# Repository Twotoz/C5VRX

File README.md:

<div align="center">

  <p><strong>ESP32-C5 Analog 5.8 GHz FPV Receiver</strong></p>
  <p>From live 5.8 GHz FPV video to real-time analog CVBS with one Seeed Studio XIAO ESP32-C5 and a passive resistor DAC.</p>

  <p>

  </p>

</div>

---

C5VRX-5 receives analog 5.8 GHz FPV video with the ESP32-C5's own radio and
outputs composite PAL/NTSC through a passive 6-bit resistor DAC: automatic
gain control, a quick baseline boot with manual calibration, an on-screen
menu, and browser-based flashing and controls.

The default demodulator is **U50P64-R1**, the U80P64-R1 formulas with loop
gain 0.50: less picture noise for a VTX of deviation up to about 1.0 at the
cost of detail and colour level. A VTX measured wider falls back to
**U80P64-R1** ([evidence and limits](docs/P64.md)), which has one positive
NTSC check. U50P64-R1 is host-tested only; PAL, weak-signal behaviour and
range still need hardware validation. Board findings, including the retired U85Q/kp/LP models
and the removed sync flywheel, are in [docs/FINDINGS.md](docs/FINDINGS.md).

## Experimental firmware — flight safety warning

> [!WARNING]
> **C5VRX is an experimental FPV receiver. Bugs, signal loss, automatic
> receive-chain changes or incompatibility with your camera/goggles can cause
> sudden loss of video or sync, even after an apparently successful test.
> Loss of FPV video can lead to a crash, property damage or serious injury.**
> Do not rely on C5VRX as your only means of maintaining safe control of an aircraft.

- **Test every firmware, hardware and settings combination on the ground
  first**, propellers removed: startup, calibration, weak signal, recovery
  after video loss, with your own camera and goggles.
- **Keep disruptive actions on the ground.** Calibration, scanning, channel
  changes, the menu, DAC tests and diagnostics can interrupt the picture;
  never flash or run bench tests in flight.
- **Automatic changes are experimental too.** Live filter/profile switching
  (default on; console `A` turns it off, `T` shows the state) and live
  OUTPUT/format changes restart part of the pipeline and may interrupt video.
- **Fly tests in a controlled area** clear of people, traffic and property,
  close by, with a safe way to recover if video disappears, and within local
  rules (visual line of sight, observers).
- **A release, a "Latest" label or green CI is not flight qualification.**
  PR builds are development builds; a test of an earlier build does not
  validate later changes.
- **Report video loss** with the exact firmware version, hardware, settings,
  steps and any logs/DVR footage, and investigate on the ground before flying
  again.

The firmware is provided under [GPL-3.0-only](LICENSE), including its warranty
and liability provisions in sections 15–17, to the extent permitted by
applicable law. This warning does not replace those terms or limit rights
that cannot legally be excluded.

## Video

[C5VRX-5 vs C5VRX-4 flight range test by Louis Hitchcock](https://www.youtube.com/watch?v=Gp3xmLrn_34).

## Hardware

A Seeed Studio XIAO ESP32-C5 and seven resistors; no extra RF parts
([schematic](docs/hardware/c5vrx-dac-schematic.png)). Six resistors, one per
pin, join on one node, the CVBS output; the seventh loads that node to GND.

| XIAO pin | GPIO | DAC bit | Resistor to the output node |
| --- | ---: | --- | ---: |
| D4 | 23 | bit 0 (LSB) | 8.2 kΩ |
| D5 | 24 | bit 1 | 3.9 kΩ |
| D6 | 11 | bit 2 | 2.0 kΩ |
| D7 | 12 | bit 3 | 1.0 kΩ |
| D8 | 8 | bit 4 | 470 Ω |
| D9 | 9 | bit 5 (MSB) | 240 Ω |
| GND | - | load | 200 Ω (output node to GND) |

```
D4 --[8.2k]--+
D5 --[3.9k]--+
D6 --[2.0k]--+
D7 --[1.0k]--+-----------> CVBS out (goggle / monitor AV-in, video)
D8 --[470R]--+     |
D9 --[240R]--+   [200R]   (optional: 470 pF from the node to GND,
                   |        improvement unproven)
GND ---------------+------> GND (goggle / monitor AV-in ground)
```

- **Pin order matters**: 8.2k on D4, 240R on D9. A swapped pair gives a
  scrambled, banded picture.
- Connect the node to the video input (tip) of the goggles, DVR or monitor,
  with a common ground. Standard E24 1 % resistors are fine; keep the wires
  short. Power comes over USB-C or the 5 V pin.
- The video level is **OUTPUT** in the menu (0.5–5.0x, saved; high levels
  can clip). EXPERIMENTAL > AUTO OUTPUT (off by default) lets it follow the
  VTX while OUTPUT is 1.0x; every change it makes is a short (~5 ms) video
  restart.
- **Check the build with the DAC self-test** (`Z` or menu DAC TEST) before
  chasing picture problems: see
  [Building and testing the resistor DAC](docs/hardware/dac-build-and-test.md).

IQ routing is internal (no wiring) and uses GPIO27 (the user LED, which may
glow) and GPIO2. The planned seven/eight-bit DAC expansion is cancelled;
firmware stays six-bit. Leave the carrier's optional R8/R9 unpopulated and
SJ2/SJ3 open.

### Optional external LNA (more range)

C5VRX-5 now supports an external low-noise amplifier in front of the
XIAO. Tested with the **Zeenko ZK06-UM** (10 MHz–6 GHz, SMA;
datasheet at 5.8 GHz: ~22.6 dB gain, ~1.0 dB noise figure), listed under
[Build components](#build-components).

- **Wiring:** antenna → LNA input → LNA output → IPX (U.FL) to SMA pigtail
  → the XIAO's IPX antenna connector (both listed under
  [Build components](#build-components)). Mind the arrow on the LNA: it
  points from the antenna to the receiver. Keep the antenna-to-LNA cable as
  short as possible: every dB lost before the LNA is lost range. Power the
  LNA as its seller specifies.
- **No setting needed.** The firmware measures its own receiver noise and
  follows it: the gain stops where the LNA's noise would fold the 4-bit IQ
  (about G67 with this LNA, G83 without), and the noise reference, signal
  meter, AGC and live DC model adapt by themselves. Fitting or removing the
  LNA needs no calibration. Let the receiver see a few seconds without a
  VTX on its channel after the first boot with a new front end.
- **What it gives:** the receiver's noise figure drops from ~6 dB to ~1 dB.
  In a first indoor walk (a small house, rooms and cupboards) the picture
  held to about **6.5 dB weaker signals** than the bare receiver on the
  previous firmware (50 % picture near −93 dBm at the antenna against
  −86.5 dBm). How much distance that is depends on the surroundings: about
  1.5–1.7× in built-up areas, more in open space; an outdoor A/B is still to
  come.
- **Close in** the LNA's extra gain uses up the lowest gain rows sooner;
  STRONG LANE (EXPERIMENTAL, on by default) takes over when even the lowest
  row folds. EXPERIMENTAL > LEVEL TOP (9 default; 6 / 12 / 16) sets how much
  noise the top gain row may carry.

Details and measurements: [docs/FINDINGS.md](docs/FINDINGS.md), "Received
level at the chip pin" and the external LNA notes.

### Optional digital video capture: Clock Pin D10

In **EXPERIMENTAL**, set **Clock Pin D10** to **ON**, then power off and
move the existing **bit 2 / 2.0 kohm branch from D6/GPIO11 to D3/GPIO7**.
On the next boot, D10/GPIO10 exports the **40 MHz PARLIO TX clock**, and
bit 2 uses D3. OFF is the default and retains the original D4-D9 wiring;
turning it off also needs a reboot and moving the branch back. The menu
shows a reboot warning until the requested setting matches the active one.
The ordinary PR firmware includes this option; no custom build is needed.

For FPGA capture, tap the data pins **before the resistors**, use 3.3 V
inputs and a common ground. With the option active, bit order low to high is
D4, D5, **D3**, D7, D8, D9. D6 is disconnected from TX. Data shifts on
falling clock edges; capture on rising edges and verify timing on your board.
The bus is still six-bit composite video: live samples are identical pairs
`[D,D]` at TX40, **20 MS/s unique codes**. The original colour burst is
preserved; the external device owns sync recovery and colour decoding.
Menu/startup rasters also use this bus. Halted TX/restarts can interrupt the
clock and video; the capture device must reacquire. Console **T** reports
`SAMPLE_CLOCK` with active/requested state, pin, rate and DAC-bit-2 pin.

This extends [LAP87's capture tests](https://github.com/Twotoz/C5VRX/issues/256#issuecomment-6530295384).
The GPIO11 bit-2 rising-edge delay reported there (25 ns) motivates the D3
route; a timing fix on D3 is **not yet verified**. GPIO2 remains IQ-owned.
DAC TEST labels bit 2 as D3 when active; in `tools/dac_check.py`, enter
that branch's measurement using the existing `--d6` argument.
USB DTR/RTS can trigger the ESP32-C5 USB-Serial-JTAG reset/boot behaviour;
there is no deliberate host-DTR gate in the video stream.

### DIY Carrier PCB — REV C: Fat Shark Module + 3.5 mm AV Jack

**[C5VRX_JACK_DIY_V3 / REV C](hardware/C5VRX_JACK_DIY_V3)** is the latest proposed DIY carrier revision for the Seeed Studio XIAO ESP32-C5. It keeps the REV B layout (Fat Shark module-bay outline, 3.5 mm PJ-320D AV jack, reserved seventh/eighth DAC branches) and replaces the SJ1 bay-power solder bridge with a through-hole 1N5819 Schottky diode, so USB and the goggle bay can be connected at the same time.

<div align="center">

</div>

| Feature | REV C details |
| --- | --- |
| **Form factor** | 42.51 × 28.80 mm; XIAO, AV jack and bay header keep their REV A positions |
| **AV output** | VIDEO on Fat Shark J1 pin 6 and PJ-320D tip + ring 1; ground on the jack sleeve |
| **Through-hole DAC** | DIN0207 axial ¼ W resistors; existing six branches and 200 Ω shunt retained |
| **Reserved DAC expansion** | R8: 15 kΩ from D10/GPIO10 via SJ2; R9: 33 kΩ from D3/GPIO7 via SJ3 |
| **Bay power** | D1: 1N5819 Schottky (DO-41, through-hole) from bay 5 V to XIAO 5 V; no jumper to open before USB programming |
| **Rear solder jumpers** | SJ2 / BIT 7 and SJ3 / BIT 8: extra DAC branches |
| **Artwork** | C5VRX logos on both sides; REV C and 6–8 BIT DAC markings on the back |

**Current firmware remains six-bit:** leave R8/R9 unpopulated and SJ2/SJ3 open. The old expansion footprints are retained in the PCB artwork only; seven/eight-bit firmware support is cancelled. Use the rewiring above for Clock Pin D10. [Assembly and jumper settings](hardware/C5VRX_JACK_DIY_V3#dac-branches-and-rear-jumpers).

**Downloads:** [Gerbers + drills](hardware/C5VRX_JACK_DIY_V3/exports/C5VRX_JACK_DIY_V3-gerbers.zip) · [KiCad project](hardware/C5VRX_JACK_DIY_V3) · [BOM](hardware/C5VRX_JACK_DIY_V3/BOM.csv) · [Schematic PDF](hardware/C5VRX_JACK_DIY_V3/exports/C5VRX_JACK_DIY_V3-schematic.pdf) · [STEP](hardware/C5VRX_JACK_DIY_V3/exports/C5VRX_JACK_DIY_V3.step) · [Renders](hardware/C5VRX_JACK_DIY_V3/exports/renders/).

KiCad ERC/DRC and schematic/PCB parity checks are clean; REV C has not been built or measured. [REV B](hardware/C5VRX_JACK_DIY_V2) and the original [REV A carrier](hardware/C5VRX_JACK_DIY) remain available with their fabrication files.

## Flashing

- **Browser:** open the [web flasher](https://twotoz.github.io/C5VRX/) in
  desktop Chrome or Edge, choose **C5VRX-5** and a build, and flash. Use
  **Full firmware** when coming from another generation. **Local File**
  flashes your own `.bin`; **Legacy builds** holds archived C5VRX-3 firmware.
- **From source:** ESP-IDF **6.0.2** (filter and DC correction need its exact
  libphy; other versions build with them disabled and a warning):

  ```sh
  idf.py build
  python tools/flash.py PORT          # e.g. COM6 or /dev/ttyACM0
  ```

  Do not use `idf.py flash` on a running receiver: its USB line reset hangs
  the board until USB and battery are removed. `tools/flash.py` enters
  download mode through the firmware instead. Useful options: `--app-only`,
  `--monitor` / `--monitor-only`, `--log FILE`, `--iq DIR` (IQ snapshots),
  `--check` (boot, `T` and `D`; fails on a crash, wrong image or chain
  fault), `--no-key` (board already in the ROM loader). After
  `sdkconfig.defaults` changes, delete `sdkconfig` and rebuild.
- **XIAO ESP32-C5HR8 with 8 MB PSRAM** (optional; the standard image also
  runs without PSRAM, this one panics without it):

  ```sh
  idf.py -B build-psram -DSDKCONFIG=sdkconfig.psram "-DSDKCONFIG_DEFAULTS=sdkconfig.defaults;sdkconfig.psram.defaults" build
  python tools/flash.py PORT --build build-psram --check
  ```

  Flash the full image when switching. Boot `heap_min` rose from ~2.1 KB to
  ~21.9 KB; PAL and long runs are pending
  ([measurements](docs/FINDINGS.md#psram-8-mb-on-the-xiao-now-mapped-board-2026-10-26)).

## First boot

1. The receiver loads saved settings or a fixed baseline; a short
   sampling-phase check runs under the boot logo. There is no automatic
   RF/DC sweep.
2. If repeated measurements show a poor baseline, the menu recommends
   **CALIBRATE**: run it on the ground, preferably with the VTX off. Full RF
   optimization (`B` / web controls) is a separate, longer bench operation.
3. Select the VTX channel or use SCAN (A1 without a saved channel).
4. **CALIBRATE → Download calibration report** in the web controls exports
   read-only board data ([protocol](docs/FASTER_CALIBRATION.md)).

## Controls

**BOOT button:** short press = next channel (menu: next item); hold 0.6 s =
open the menu (menu: select).

**Menu**, one list with every value in view: BAND, CHANNEL, SCAN, VIDEO
(AUTO/NTSC/PAL), FILTER (AUTO/XNARROW/NARROW/NORMAL/WIDE), PHY FILT
(digital filter mode), AFC (ON/OFF), CALIBRATE, OUTPUT (0.5–5.0x), GAIN
(LEVEL/KEEL/RSSI/MAX/fixed), DEMOD (P64/U85Q/U50), DAC TEST, EXIT. It closes after 30 s of
inactivity (5 min in DAC TEST); entering and leaving can interrupt video.
GAIN defaults to **LEVEL**; KEEL and RSSI are kept for comparison
([AGC research](docs/FINDINGS.md)). The automatic models are remembered
across reboots; MAX and fixed gains never are.

**Serial console** (web flasher **Terminal** tab, or 115200 baud): keys are
case-sensitive, without Enter; `h` lists what your firmware supports.

| Key | Action |
| --- | --- |
| `T` / `h` | Status / help |
| `b` / `c` / `s` | Next band / next channel / scan |
| `o` / `n` / `x` / `e` | Open menu / next item / select / exit |
| `v` / `g` / `G` | Video standard / output level / gain |
| `F` / `B` / `C` | Calibrate current filter / full RF optimization / read-only calibration report |
| `Z` | DAC self-test (ground only) |
| `D` / `R` | Health report / per-second field diagnostics |
| `I` / `M` / `L` | IQ snapshot / gain map / bench IQ lane test |
| `A` | Live filter/profile switching on/off (saved) |
| `S` + suite | Bench PHY sensitivity lab, VTX on ([docs](docs/PHY_SENSITIVITY_LAB.md); ground only) |
| `` ` `` | USB download mode |

Live OUTPUT and profile changes share a five-second cooldown and a verified
restart with rollback. The browser terminal and the flasher use the port one
at a time; **Download log** saves the last 120,000 characters.

## Documentation and development

- [DAC build and self-test](docs/hardware/dac-build-and-test.md) ·
  carriers [REV C](hardware/C5VRX_JACK_DIY_V3), [REV B](hardware/C5VRX_JACK_DIY_V2), [REV A](hardware/C5VRX_JACK_DIY)
- [Receiver findings and hardware evidence](docs/FINDINGS.md) ·
  [field-test protocol](docs/FIELD_TEST.md) ·
  [current receiver behaviour](docs/PR212.md)
- [Research ledger](docs/RESEARCH_LEDGER.md) · [research index](research/README.md) ·
  [U85Q research](docs/pr190-key-findings.md) · [contributing](CONTRIBUTING.md)

`main/` is the C5VRX-5 firmware, `web/` the flasher, `test/` host tests,
`docs/` guides and findings, `research/` experiments, `tools/` console and CI
helpers; `legacy/` keeps C5VRX-1 to C5VRX-4 for reference (not built).

CI runs the host and research checks, builds with ESP-IDF 6.0.2 and publishes
`c5vrx5-v5.0.N` releases from `main` and `c5vrx5-pr-N` builds for PRs;
website-only changes create no firmware. Firmware PRs need board tests on the
matching build: host tests do not establish picture compatibility or range.

## Community

Share build photos, questions and feedback on the
[C5VRX Discord](https://discord.gg/3YNgJRHmzD).

## Credits and license

C5VRX-5 is part of [C5VRX](https://github.com/Twotoz/C5VRX) by Twotoz and
the C5VRX contributors; the official website
([twotoz.github.io/C5VRX](https://twotoz.github.io/C5VRX/)) has the project
and its Discord invite. It builds on C5VRX-2..4 (the continuous MODEM_DIAG
to BitScrambler video path, Direct Gain V3-V5, the PAIR schedule and the
U85Q study of PR #190), on zerowidth/C5VRX PR #3 (interference-burst gate,
sampling-phase probe, off-grid channel tuning), on Louis Hitchcock's staged
overload recovery (C5VRX #182/#184), and on ESPARGOS esp-sdr (GPL-3.0) for
the C5 RX filter control. Espressif supplied the GDMA EOF fix
(espressif/esp-idf#19091).

Like the rest of this repository, C5VRX-5 is licensed under
**GPL-3.0-only** (see [LICENSE](LICENSE)). The GPL allows
commercial use, including selling receivers with this firmware, provided
the source (with your changes) is passed on under the same license.

The C5VRX name and logos have separate terms; see [assets/BRANDING.md](assets/BRANDING.md).

## Build components

| Product | Photo | Link / Source |
| --- | --- | --- |
| Seeed Studio XIAO ESP32-C5 |  | [View on Amazon](https://link.amazon/B0gopCVDt) |
| C5VRX_JACK_DIY_V3 / REV C carrier |  | [Gerbers & KiCad files](hardware/C5VRX_JACK_DIY_V3) · [REV B](hardware/C5VRX_JACK_DIY_V2) · [REV A](hardware/C5VRX_JACK_DIY) |
| Perfboard (alternative) |  | [View on Amazon](https://link.amazon/B0i2qqMeq) |
| Resistor kit |  | [View on Amazon](https://link.amazon/B06XSBkln) |
| Zeenko ZK06-UM LNA (optional, [more range](#optional-external-lna-more-range)) |  | [View on Amazon](https://link.amazon/B0iY2ccnV) |
| IPX (U.FL) to SMA pigtail (XIAO to the LNA) |  | [View on Amazon](https://link.amazon/B07pMkNyf) |

Affiliate links. As an Amazon Associate, I earn from qualifying purchases.
All affiliate earnings go back into C5VRX development.

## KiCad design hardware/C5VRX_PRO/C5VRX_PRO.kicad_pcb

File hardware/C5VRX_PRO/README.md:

# C5VRX PRO — stand-alone Fat Shark receiver

**Revision A is an engineering review, not an approved PCBWay order.**
This is a component-level ESP32-C5 design in the exact DIY V3 board outline,
with the same nine bay contact positions and functions. No XIAO is used.

| Item | Implementation |
|---|---|
| Outline | 42.51 × 28.80 mm, inherited 2 mm corners, 1.6 mm board |
| Core | ESP32-C5HR2 QFN48, 2 MB in-package PSRAM, 8 MB external flash, 48 MHz crystal |
| Antenna | **Vertical SMA female**, Amphenol 132134; antenna perpendicular to the PCB |
| RF front end | QPL9504, two PE42422 switches, passive default bypass |
| BPF | Optional post-LNA Murata 4.90–5.85 GHz filter, DNP by default |
| Video | Existing six weighted DAC branches and 200 Ω shunt; seventh 15 kΩ branch reserved |
| Controls | One-ADC five-way joystick, separate BOOT and RESET |
| USB | Native USB Serial/JTAG over USB-C, two CC resistors, USBLC6 ESD |
| Power | Diode-isolated USB/bay supplies, bay PTC, exposed-pad 3.3 V LDO |
| Buzzer | Independent GPIO and optional piezo/MOSFET/discharge resistor; DNP |

The USB-C connector replaces the DIY board's large TRRS jack. CVBS remains
on bay pin 6 and TP1. There are **no GPIO-selection solder bridges**: the
joystick, optional buzzer and reserved seventh DAC branch have separate pins.

## Review files

- [Component selection](COMPONENTS.md) and [complete assembly BOM](BOM.csv).
- [KiCad project](C5VRX_PRO.kicad_pro), [PCB](C5VRX_PRO.kicad_pcb),
  [seven-page schematic PDF](exports/C5VRX_PRO-schematic.pdf).
- Mechanical assembly: [STEP](exports/C5VRX_PRO.step), [GLB](exports/C5VRX_PRO.glb).
- [3000 × 2200 render gallery](exports/renders/) and [render ZIP](exports/C5VRX_PRO-renders.zip).
- Actual [DRC/parity report](validation/drc.json), [ERC report](validation/erc.json),
  [design audit](validation/design-audit.json).
- [PCBWay fabrication and bring-up requirements](FABRICATION.md).

The gallery and assembly models are exported from this PCB, not generated
product illustrations. DNP components are absent from the default assembly.
The custom STEP models are **parametric package envelopes**, with illustrative
SMA thread rings and simplified USB/joystick bodies. They are not certified
supplier CAD or proof of enclosure clearance. The board outline and bay pads,
in contrast, are compared directly against the existing DIY V3 CAD.

## GPIO and firmware contract

| Role | GPIOs / behavior |
|---|---|
| Q nibble | 1, 0, 25, 2, low to high |
| I nibble | 27, 5, 3, 4, low to high |
| Existing DAC bits 0–5 | 23, 24, 11, 12, 8, 9 |
| Future seventh new LSB | 10 through R8, DNP |
| Joystick | **6 / ADC1_CH5**, 10 kΩ pull-up and 22 kΩ fixed pull-down |
| Optional buzzer | **7**, MOSFET gate; external pull-down |
| RF path select | **26**; low = passive bypass, high = LNA path |
| Native USB | 13 = D−, 14 = D+ |
| BOOT | 28, active low; 10 kΩ pull-up |
| RESET | CHIP_PU, active low; 10 kΩ / 1 µF startup RC |

These are real ESP32-C5 numbers, not XIAO silk labels. IQ is internal GPIO
matrix routing: those pins intentionally have no external signal traces.
GPIO27 retains a boot pull-up so BOOT-low selects USB download rather than
the USB-disabled download mode. Flash and PSRAM pins are never user IO.

The current C5VRX-5 pin map and six-bit video interface are retained. This PR
does **not** integrate a joystick driver, buzzer driver, RF switching policy
or seven-bit demodulator into the flight firmware. Existing firmware leaves
GPIO26 pulled low and therefore uses the passive RF path. Do not assume the
LNA is active merely because it is fitted. This hardware needs its own
board-specific firmware integration and board validation before production.

Joystick nominal levels at 3.3 V are approximately 0.007 V (press), 0.288 V
(up), 0.550 V (down), 0.922 V (left), 1.345 V (right), 2.269 V (released).
Calibrate real ADC thresholds with attenuation enabled, filter/debounce on the
slow control task, reject unknown levels, and support one direction at a time.
Joystick polling must never pace PARLIO or RF samples. Button directions
must be confirmed against the switch orientation on the assembled board.

The RF path must stay bypassed before any PHY initialization, calibration,
retune, restore or shutdown that might transmit. Enable the LNA only after
receive-only state is established; return to bypass on every failure. Audit
all vendor PHY call paths rather than adding an unconditional enable after
boot. External gain changes invalidate receiver noise/gain/DC calibration
provenance. Bypass/LNA switching needs explicit measured state transitions.

Seventh-bit operation requires firmware that emits seven meaningful bits,
shifts the existing six branches up one place, and remaps their significance.
Fitting R8 alone does not add resolution. No sensitivity/range improvement
is claimed from the wider DAC or the LNA's headline specifications.

## Evidence and remaining engineering

The digital checks cover pad/net correspondence, board mechanics, pin roles,
basic DAC/joystick circuit calculations, KiCad clearance/connectivity and
schematic parity. Seven ERC singleton-label warnings document the internal IQ
pins; the symbols use passive pin types, so ERC does not prove power-driver
or MCU pin-function correctness. The pin tables still require independent
datasheet review.

Routing includes a general-purpose routing pass and subsequent ground/width
cleanup. **The RF traces are not yet an approved 50 Ω layout, and USB is not
yet an approved 90 Ω differential route.** A passing connectivity DRC does
not change this. RF layer transitions, launch/matching, branch stubs, ground
returns, power necks and differential routing require manual optimization
against an agreed PCBWay stackup. No order-ready Gerber bundle is supplied
while those release blockers remain. See [FABRICATION.md](FABRICATION.md).

No board has been fabricated, assembled, flashed, measured or fitted in a
goggle bay. Final BOM sourcing, exact supplier footprints, RF performance,
LDO temperature, boot reliability, USB compliance and loaded video quality
remain unqualified. The draft PR is the place to review this first hardware
revision; it is not a production sign-off.

## Rebuilding

Requires KiCad 10 (tested CLI/API 10.0.6), Python 3.13 with CadQuery 2.8.0,
and optionally Freerouting 2.5.0 / Java 25. `KICAD_INSTALL` and `KICAD_CLI`
override the Windows defaults in the tools.

1. `python tools/build_models.py`
2. Run `tools/build_board.py` with KiCad's Python. This intentionally resets routing.
3. `python tools/build_schematic.py`; export the XML netlist to `validation/schematic.xml`.
4. Run `tools/route_board.py prepare` with KiCad Python, route the DSN, then
   `tools/route_board.py import`. The saved SES is the routing checkpoint.
5. Run `tools/finish_board.py` with KiCad Python, then KiCad DRC with
   `--schematic-parity` and ERC. Run `tools/check_design.py` with KiCad Python.
6. `python tools/export_review.py` exports the PDF, assembly and gallery.

Routing environment used: `FREEROUTING__ROUTER__AUTOMATIC_NECKDOWN=false`,
`FREEROUTING__ROUTER__FANOUT__MAX_PASSES=3`, CLI `-mp 30 -mt 4`.
The final pass enforces 0.127 mm minimum traces and removes external IQ stubs.

## Attribution

This design extends **C5VRX by Twotoz and the C5VRX contributors**, especially
the DIY V3 mechanical interface and passive DAC, at base commit
`e0f49b5`. [Canonical source](https://github.com/Twotoz/C5VRX);
[official website and Discord invite](https://twotoz.github.io/C5VRX/).
Covered project material remains under [GPL-3.0-only](../../LICENSE);
separate [branding terms](../../assets/BRANDING.md) remain applicable.
Vendor facts and footprint/model provenance are in [SOURCES.md](SOURCES.md).

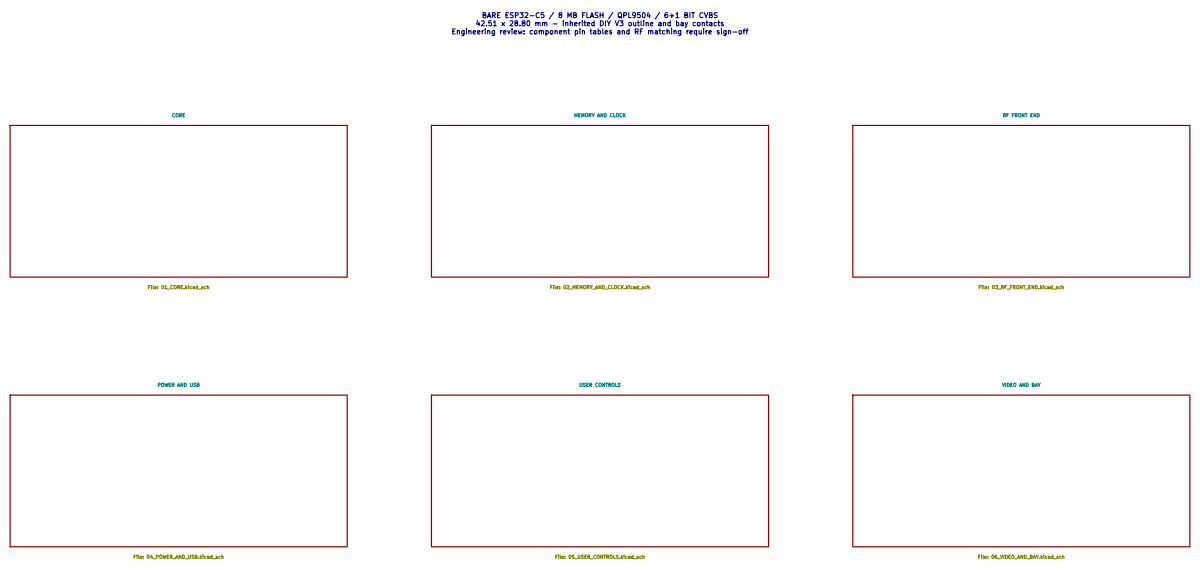
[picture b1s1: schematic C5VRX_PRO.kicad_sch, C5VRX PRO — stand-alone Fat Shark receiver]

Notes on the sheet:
BARE ESP32-C5 / 8 MB FLASH / QPL9504 / 6+1 BIT CVBS 42.51 x 28.80 mm - inherited DIY V3 outline and bay contacts Engineering review: component pin tables and RF matching require sign-off

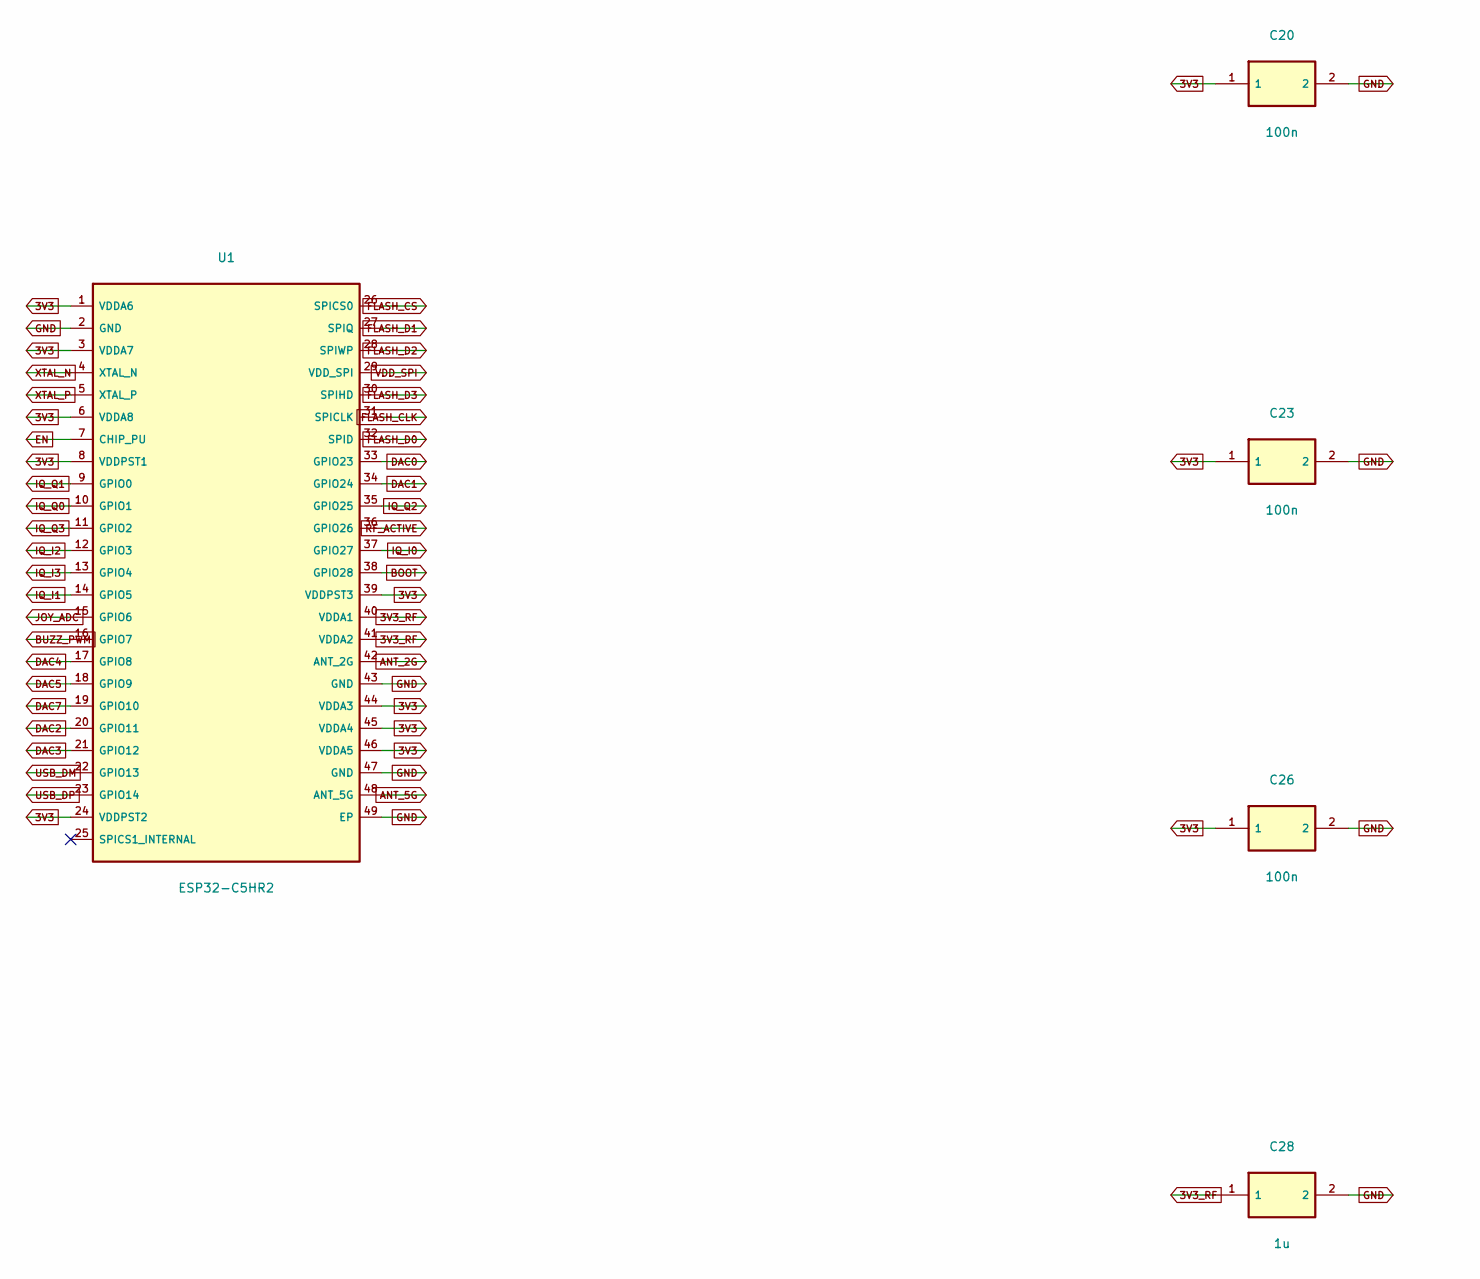
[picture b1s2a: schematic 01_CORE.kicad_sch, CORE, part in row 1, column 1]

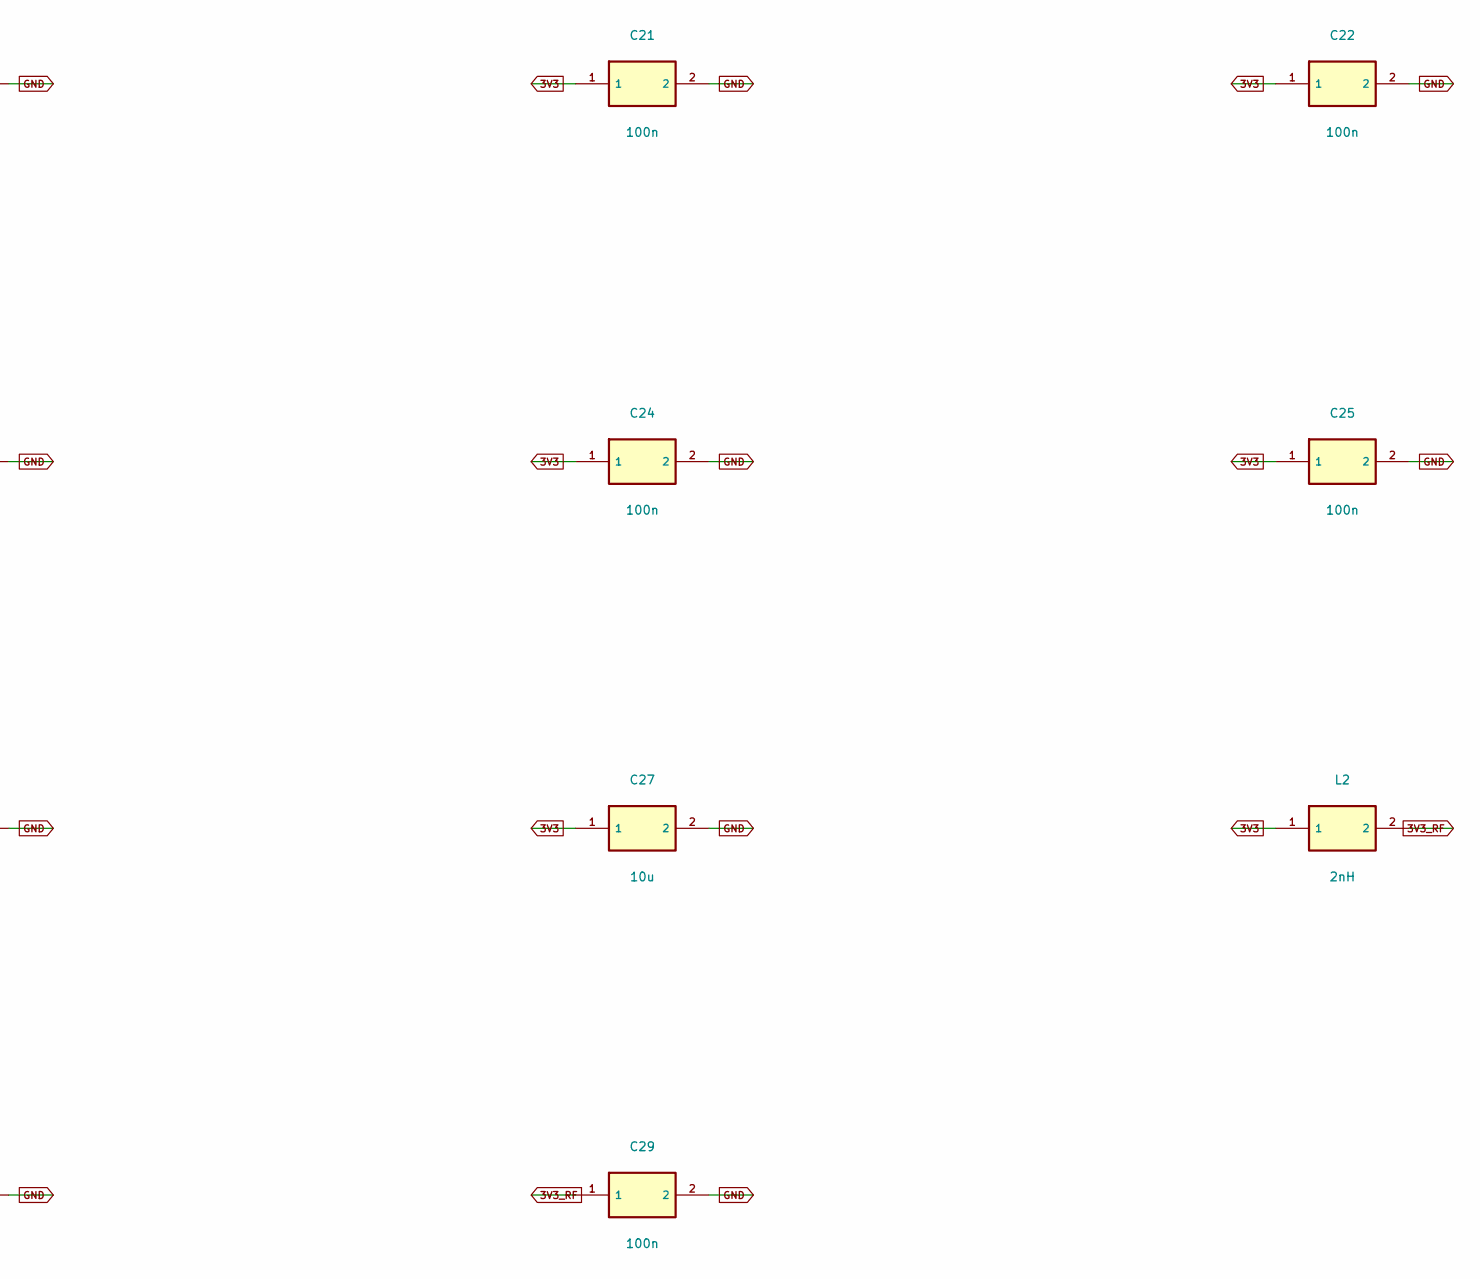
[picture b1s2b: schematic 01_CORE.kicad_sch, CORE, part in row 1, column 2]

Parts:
C20, C21, C22, C23, C24, C25, C26, C29: 100n; Capacitor_SMD__C_0402_1005Metric; MPN GRM155R71C104KA88D
C27: 10u; Capacitor_SMD__C_0603_1608Metric; MPN GRM188R61A106KE69D
C28: 1u; Capacitor_SMD__C_0402_1005Metric; MPN GRM155R61A105KE15D
L2: 2nH; Inductor_SMD__L_0402_1005Metric; MPN LQG15HS2N0S02D
U1: ESP32-C5HR2; Package_DFN_QFN__QFN-48-1EP_6x6mm_P0.4mm_EP4.6x4.6mm; MPN ESP32-C5HR2

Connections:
3V3: C20.1, C21.1, C22.1, C23.1, C24.1, C25.1, C26.1, C27.1, L2.1, U1.1 (VDDA6), U1.3 (VDDA7), U1.6 (VDDA8), U1.8 (VDDPST1), U1.24 (VDDPST2), U1.39 (VDDPST3), U1.44 (VDDA3), U1.45 (VDDA4), U1.46 (VDDA5); also elsewhere on the board
3V3_RF: C28.1, C29.1, L2.2, U1.40 (VDDA1), U1.41 (VDDA2)
ANT_2G: U1.42 (ANT_2G); also elsewhere on the board
ANT_5G: U1.48 (ANT_5G); also elsewhere on the board
BOOT: U1.38 (GPIO28); also elsewhere on the board
BUZZ_PWM: U1.16 (GPIO7); also elsewhere on the board
DAC0: U1.33 (GPIO23); also elsewhere on the board
DAC1: U1.34 (GPIO24); also elsewhere on the board
DAC2: U1.20 (GPIO11); also elsewhere on the board
DAC3: U1.21 (GPIO12); also elsewhere on the board
DAC4: U1.17 (GPIO8); also elsewhere on the board
DAC5: U1.18 (GPIO9); also elsewhere on the board
DAC7: U1.19 (GPIO10); also elsewhere on the board
EN: U1.7 (CHIP_PU); also elsewhere on the board
FLASH_CLK: U1.31 (SPICLK); also elsewhere on the board
FLASH_CS: U1.26 (SPICS0); also elsewhere on the board
FLASH_D0: U1.32 (SPID); also elsewhere on the board
FLASH_D1: U1.27 (SPIQ); also elsewhere on the board
FLASH_D2: U1.28 (SPIWP); also elsewhere on the board
FLASH_D3: U1.30 (SPIHD); also elsewhere on the board
GND: C20.2, C21.2, C22.2, C23.2, C24.2, C25.2, C26.2, C27.2, C28.2, C29.2, U1.2 (GND), U1.43 (GND), U1.47 (GND), U1.49 (EP); also elsewhere on the board
IQ_I0: U1.37 (GPIO27); also elsewhere on the board
IQ_I1: U1.14 (GPIO5)
IQ_I2: U1.12 (GPIO3)
IQ_I3: U1.13 (GPIO4)
IQ_Q0: U1.10 (GPIO1)
IQ_Q1: U1.9 (GPIO0)
IQ_Q2: U1.35 (GPIO25)
IQ_Q3: U1.11 (GPIO2)
JOY_ADC: U1.15 (GPIO6); also elsewhere on the board
RF_ACTIVE: U1.36 (GPIO26); also elsewhere on the board
USB_DM: U1.22 (GPIO13); also elsewhere on the board
USB_DP: U1.23 (GPIO14); also elsewhere on the board
VDD_SPI: U1.29 (VDD_SPI); also elsewhere on the board
XTAL_N: U1.4 (XTAL_N); also elsewhere on the board
XTAL_P: U1.5 (XTAL_P); also elsewhere on the board

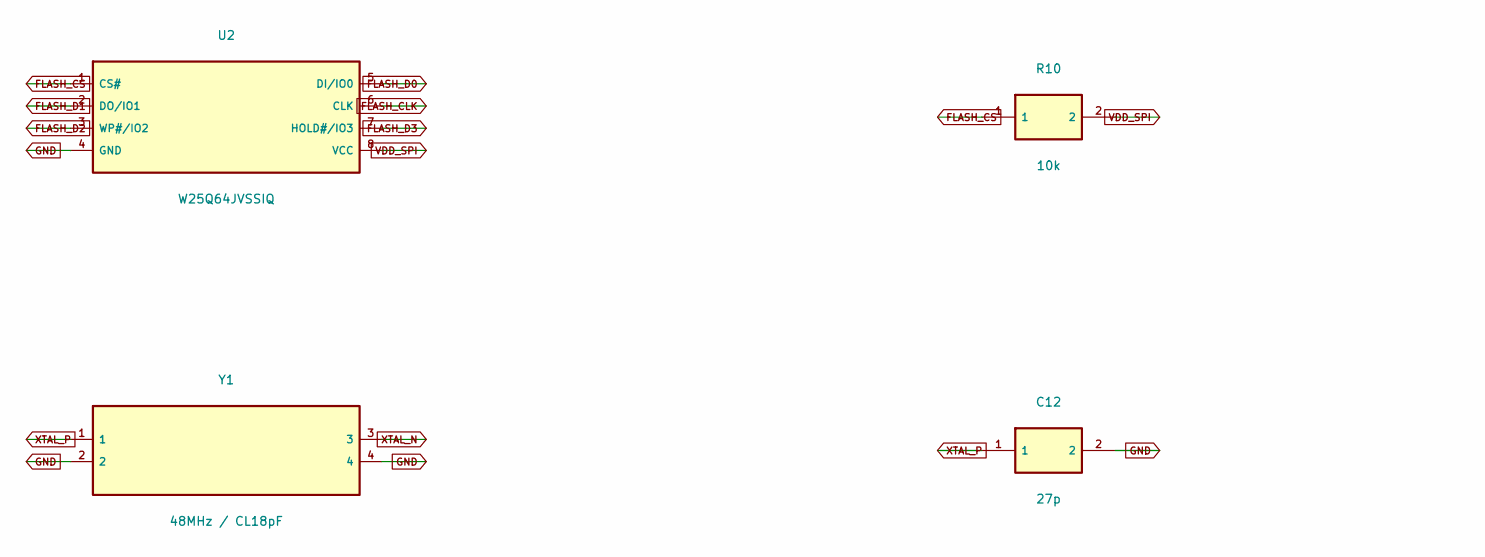
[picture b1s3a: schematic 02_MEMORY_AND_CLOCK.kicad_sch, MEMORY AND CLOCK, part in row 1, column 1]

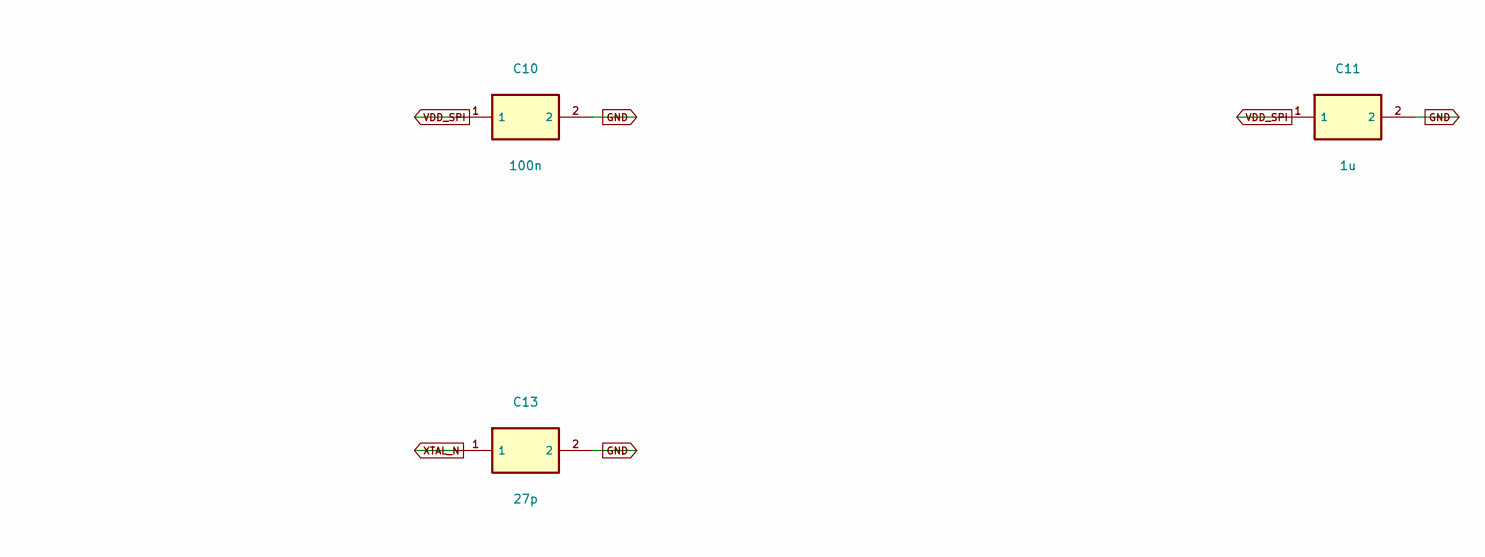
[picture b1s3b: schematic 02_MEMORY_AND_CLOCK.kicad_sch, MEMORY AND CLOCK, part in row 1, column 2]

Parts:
C10: 100n; Capacitor_SMD__C_0402_1005Metric; MPN GRM155R71C104KA88D
C11: 1u; Capacitor_SMD__C_0402_1005Metric; MPN GRM155R61A105KE15D
C12, C13: 27p; Capacitor_SMD__C_0402_1005Metric; MPN GRM1555C1H270JA01D
R10: 10k; Resistor_SMD__R_0402_1005Metric; MPN RC0402FR-0710KL
U2: W25Q64JVSSIQ; Package_SO__SOIC-8_3.9x4.9mm_P1.27mm; MPN W25Q64JVSSIQ
Y1: 48MHz / CL18pF; Crystal__Crystal_SMD_3225-4Pin_3.2x2.5mm; MPN ABM8-48.000MHZ-B2-T

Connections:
FLASH_CLK: U2.6 (CLK); also elsewhere on the board
FLASH_CS: R10.1, U2.1 (CS#); also elsewhere on the board
FLASH_D0: U2.5 (DI/IO0); also elsewhere on the board
FLASH_D1: U2.2 (DO/IO1); also elsewhere on the board
FLASH_D2: U2.3 (WP#/IO2); also elsewhere on the board
FLASH_D3: U2.7 (HOLD#/IO3); also elsewhere on the board
GND: C10.2, C11.2, C12.2, C13.2, U2.4 (GND), Y1.2, Y1.4; also elsewhere on the board
VDD_SPI: C10.1, C11.1, R10.2, U2.8 (VCC); also elsewhere on the board
XTAL_N: C13.1, Y1.3; also elsewhere on the board
XTAL_P: C12.1, Y1.1; also elsewhere on the board

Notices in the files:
hardware/C5VRX_PRO/tools/build_board.py:
SPDX-License-Identifier: GPL-3.0-only
parts and their libraries:
License: Apache-2.0
